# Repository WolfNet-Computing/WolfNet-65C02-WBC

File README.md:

[Pictures](./pictures.html)  
[Connector Pinouts](./pinouts.html)  
[Memory Map](./memory_map.html)  
[Thanks](./thanks.html)

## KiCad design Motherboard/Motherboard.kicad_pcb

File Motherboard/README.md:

# WN-6502-WBC Motherboard

## Pinouts

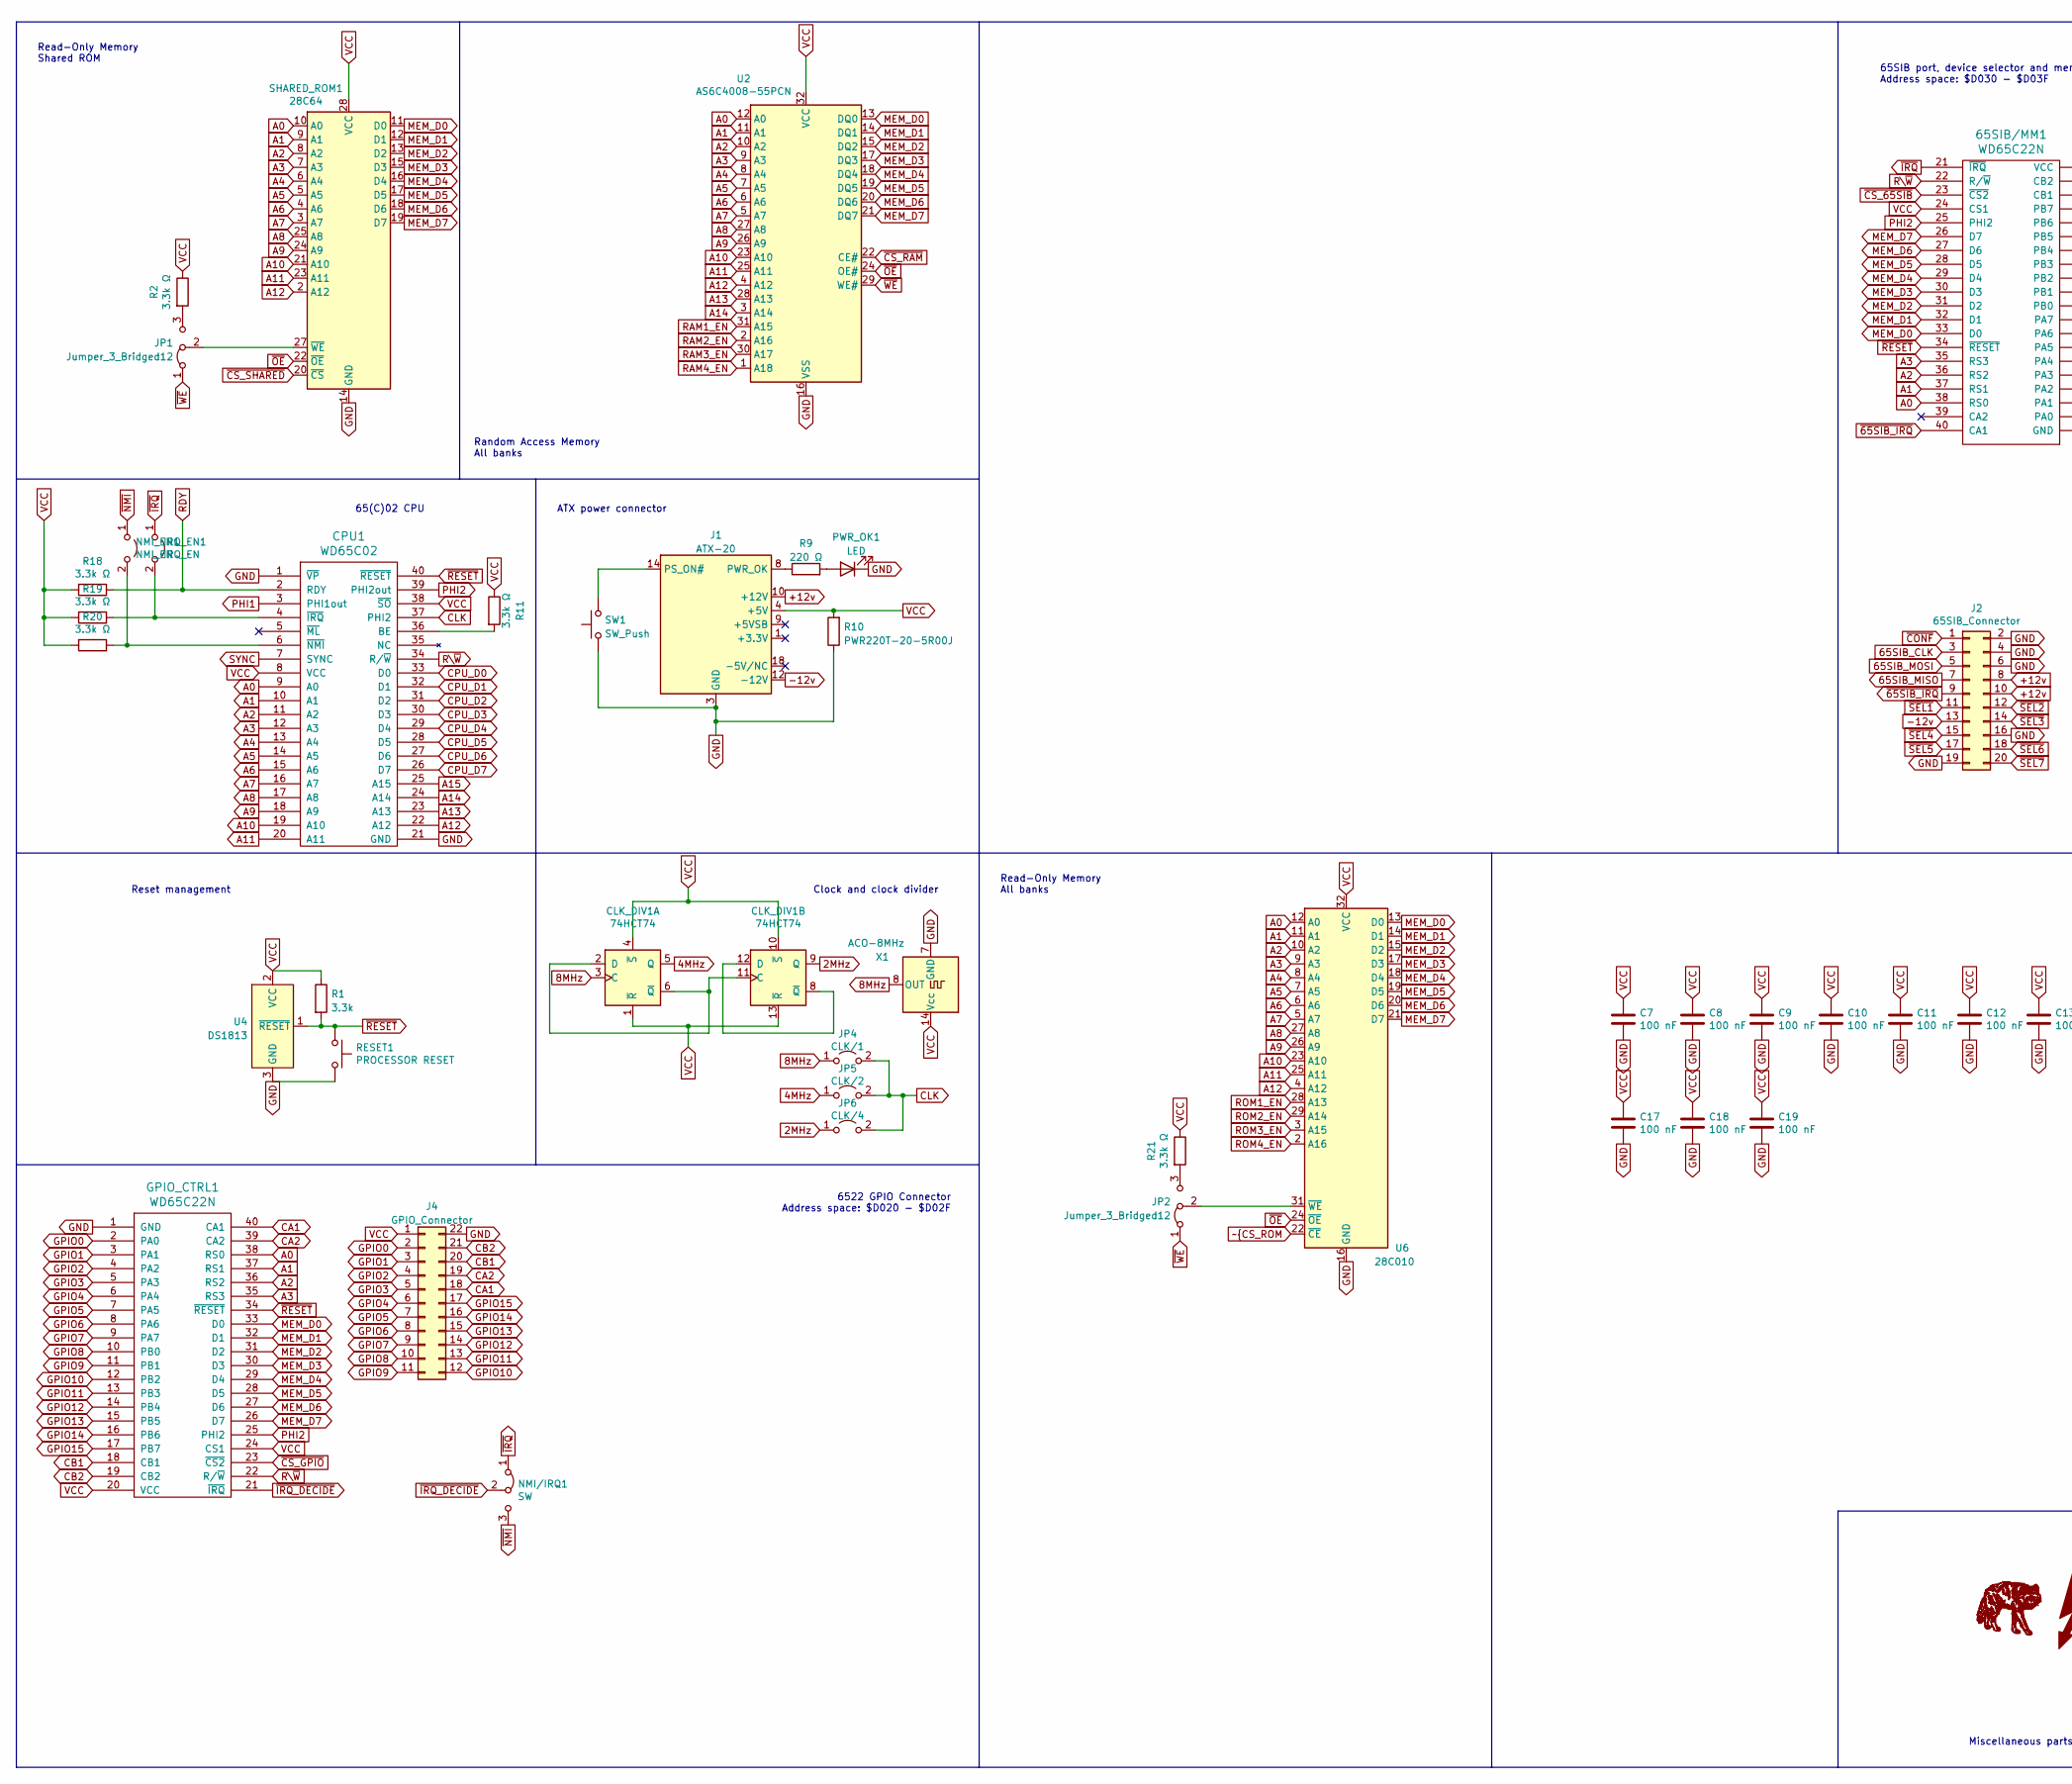
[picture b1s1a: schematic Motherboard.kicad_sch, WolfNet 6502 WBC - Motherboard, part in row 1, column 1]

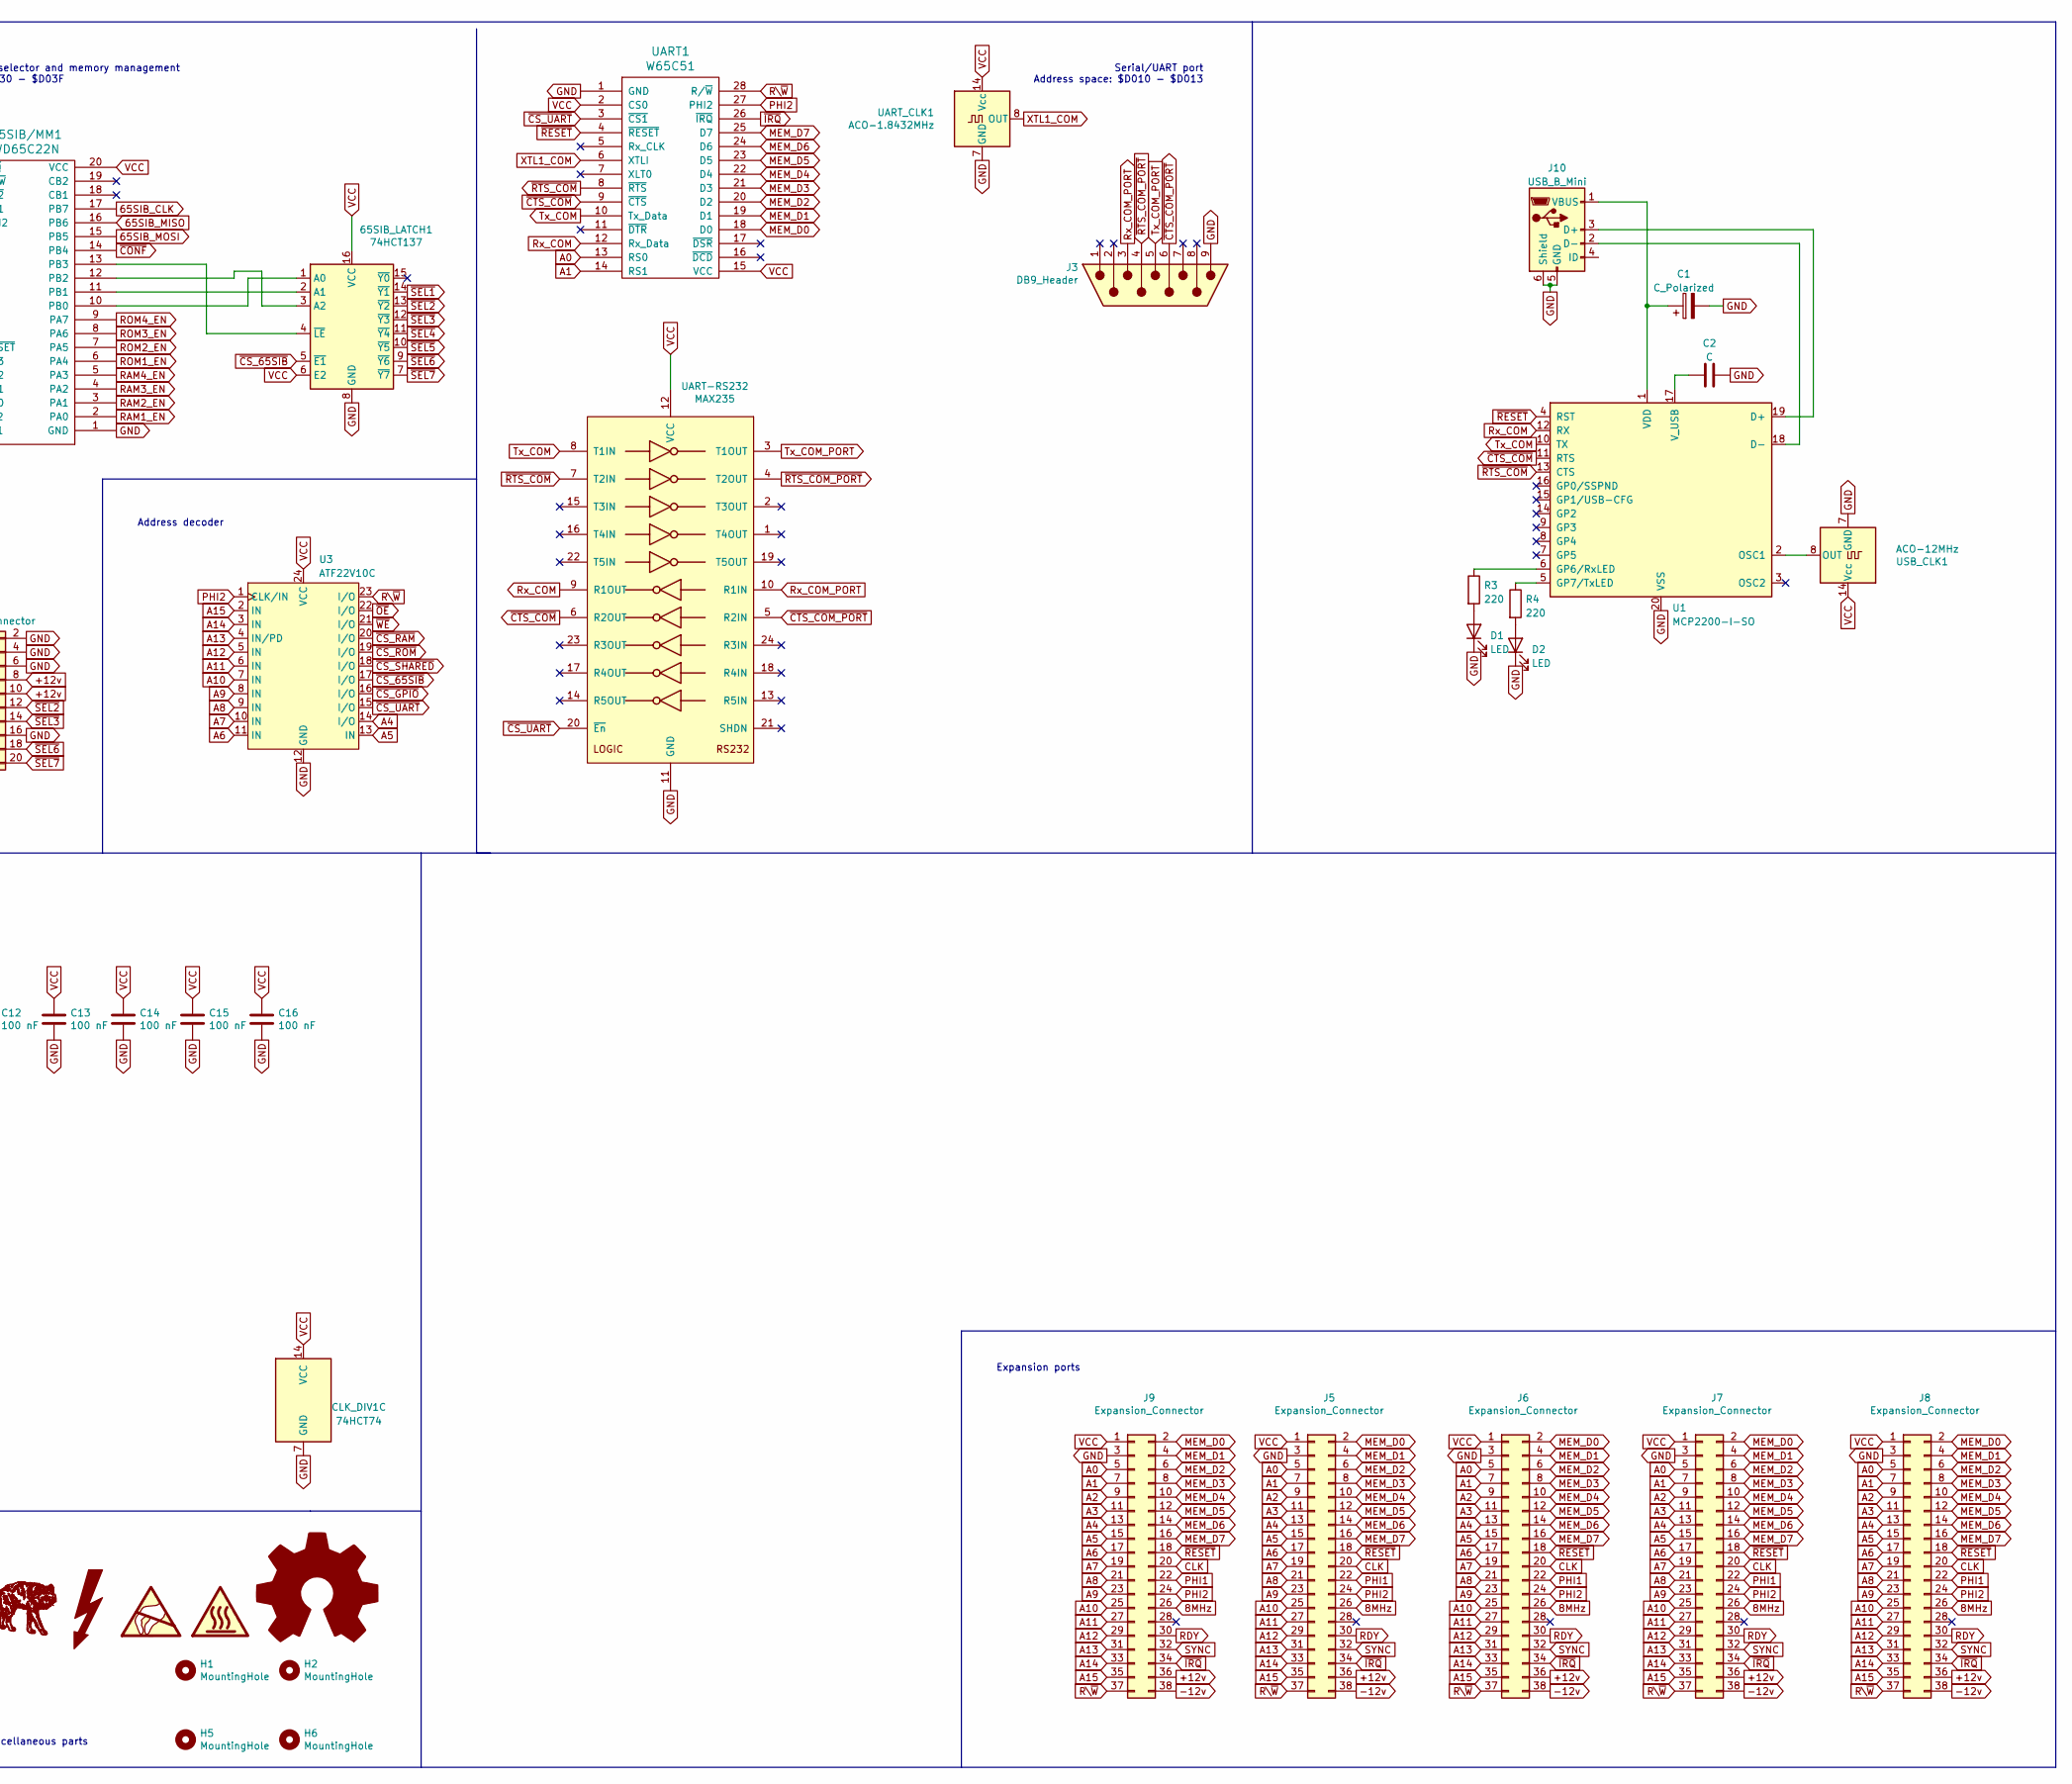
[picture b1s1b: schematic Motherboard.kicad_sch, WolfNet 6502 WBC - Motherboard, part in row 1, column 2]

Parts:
65SIB/MM1: WD65C22N; DIP-40_W15.24mm_Socket_LongPads
65SIB_LATCH1: 74HCT137; DIP-16_W7.62mm_Socket_LongPads
C1: C_Polarized; CP_Radial_D5.0mm_P2.50mm
C2: C; C_Disc_D3.0mm_W1.6mm_P2.50mm
C7, C8, C9, C10, C11, C12, C13, C14, C15, C16, C17, C18, C19: 100 nF; C_Disc_D3.0mm_W1.6mm_P2.50mm
CLK_DIV1: 74HCT74; DIP-14_W7.62mm_Socket_LongPads
CPU1: WD65C02; DIP-40_W15.24mm_Socket_LongPads
D1, D2: LED; LED_D5.0mm
GPIO_CTRL1: WD65C22N; DIP-40_W15.24mm_Socket_LongPads
H1, H2, H5, H6: MountingHole; MountingHole_3.2mm_M3
IRQ_EN1: IRQ_EN; PinHeader_1x02_P2.54mm_Vertical
J1: ATX-20; Molex_Mini-Fit_Jr_5566-20A_2x10_P4.20mm_Vertical
J2: 65SIB_Connector; IDC-Header_2x10-1MP_P2.54mm_Latch6.5mm_Vertical
J3: DB9_Header
J4: GPIO_Connector; PinHeader_2x11_P2.54mm_Vertical
J5, J6, J7, J8, J9: Expansion_Connector; Expansion_Connector_Motherboard
J10: USB_B_Mini; USB_Mini-B_Tensility_54-00023_Vertical
JP1, JP2: Jumper_3_Bridged12; PinHeader_1x03_P2.54mm_Vertical
JP4: CLK/1; PinHeader_1x02_P2.54mm_Vertical
JP5: CLK/2; PinHeader_1x02_P2.54mm_Vertical
JP6: CLK/4; PinHeader_1x02_P2.54mm_Vertical
NMI/IRQ1: SW; PinHeader_1x03_P2.54mm_Vertical
NMI_EN1: NMI_EN; PinHeader_1x02_P2.54mm_Vertical
PWR_OK1: LED; LED_D5.0mm
R1: 3.3k; R_Axial_DIN0207_L6.3mm_D2.5mm_P7.62mm_Horizontal
R2, R11, R18, R19, R20, R21: 3.3k Ω; R_Axial_DIN0207_L6.3mm_D2.5mm_P7.62mm_Horizontal
R3, R4: 220; R_Axial_DIN0207_L6.3mm_D2.5mm_P7.62mm_Horizontal
R9: 220 Ω; R_Axial_DIN0207_L6.3mm_D2.5mm_P7.62mm_Horizontal
R10: PWR220T-20-5R00J; TO-220-2_Horizontal_TabDown
RESET1: PROCESSOR RESET; SW_PUSH_6mm_H4.3mm
SHARED_ROM1: 28C64; DIP_Socket-28_W11.9_W12.7_W15.24_W17.78_W18.5_3M_228-1277-0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
SW1: SW_Push; SW_PUSH_6mm
U1: MCP2200-I-SO; SOIC-20W_7.5x12.8mm_P1.27mm
U2: AS6C4008-55PCN; DIP-32_W15.24mm
U3: ATF22V10C; DIP-24_W7.62mm_Socket_LongPads
U4: DS1813; TO-92
U6: 28C010; DIP_Socket-32_W11.9_W12.7_W15.24_W17.78_W18.5_3M_232-1285-0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
UART1: W65C51; DIP-28_W15.24mm_Socket_LongPads
UART-RS232: MAX235; DIP-24_W15.24mm_Socket_LongPads
UART_CLK1: ACO-1.8432MHz; Oscillator_DIP-14
USB_CLK1: ACO-12MHz; Oscillator_DIP-14
X1: ACO-8MHz; Oscillator_DIP-14

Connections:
2MHz: CLK_DIV1.9 (Q), JP6.1 (A)
4MHz: CLK_DIV1.5 (Q), JP5.1 (A)
8MHz: CLK_DIV1.3 (C), J5.26, J6.26, J7.26, J8.26, J9.26, JP4.1 (A), X1.8 (OUT)
65SIB_CLK: 65SIB/MM1.17 (PB7), J2.3 (CLK)
65SIB_MISO: 65SIB/MM1.16 (PB6), J2.7 (MISO)
65SIB_MOSI: 65SIB/MM1.15 (PB5), J2.5 (MOSI)
+12v: J1.10 (+12V), J2.8 (12v), J2.10 (12v), J5.36, J6.36, J7.36, J8.36, J9.36
-12v: J1.12 (-12V), J2.13 (-12v), J5.38, J6.38, J7.38, J8.38, J9.38
A0: 65SIB/MM1.38 (RS0), CPU1.9 (A0), GPIO_CTRL1.38 (RS0), J5.5, J6.5, J7.5, J8.5, J9.5, SHARED_ROM1.10 (A0), U2.12 (A0), U6.12 (A0), UART1.13 (RS0)
A1: 65SIB/MM1.37 (RS1), CPU1.10 (A1), GPIO_CTRL1.37 (RS1), J5.7, J6.7, J7.7, J8.7, J9.7, SHARED_ROM1.9 (A1), U2.11 (A1), U6.11 (A1), UART1.14 (RS1)
A2: 65SIB/MM1.36 (RS2), CPU1.11 (A2), GPIO_CTRL1.36 (RS2), J5.9, J6.9, J7.9, J8.9, J9.9, SHARED_ROM1.8 (A2), U2.10 (A2), U6.10 (A2)
A3: 65SIB/MM1.35 (RS3), CPU1.12 (A3), GPIO_CTRL1.35 (RS3), J5.11, J6.11, J7.11, J8.11, J9.11, SHARED_ROM1.7 (A3), U2.9 (A3), U6.9 (A3)
A4: CPU1.13 (A4), J5.13, J6.13, J7.13, J8.13, J9.13, SHARED_ROM1.6 (A4), U2.8 (A4), U3.14 (I/O), U6.8 (A4)
A5: CPU1.14 (A5), J5.15, J6.15, J7.15, J8.15, J9.15, SHARED_ROM1.5 (A5), U2.7 (A5), U3.13 (IN), U6.7 (A5)
A6: CPU1.15 (A6), J5.17, J6.17, J7.17, J8.17, J9.17, SHARED_ROM1.4 (A6), U2.6 (A6), U3.11 (IN), U6.6 (A6)
A7: CPU1.16 (A7), J5.19, J6.19, J7.19, J8.19, J9.19, SHARED_ROM1.3 (A7), U2.5 (A7), U3.10 (IN), U6.5 (A7)
A8: CPU1.17 (A8), J5.21, J6.21, J7.21, J8.21, J9.21, SHARED_ROM1.25 (A8), U2.27 (A8), U3.9 (IN), U6.27 (A8)
A9: CPU1.18 (A9), J5.23, J6.23, J7.23, J8.23, J9.23, SHARED_ROM1.24 (A9), U2.26 (A9), U3.8 (IN), U6.26 (A9)
A10: CPU1.19 (A10), J5.25, J6.25, J7.25, J8.25, J9.25, SHARED_ROM1.21 (A10), U2.23 (A10), U3.7 (IN), U6.23 (A10)
A11: CPU1.20 (A11), J5.27, J6.27, J7.27, J8.27, J9.27, SHARED_ROM1.23 (A11), U2.25 (A11), U3.6 (IN), U6.25 (A11)
A12: CPU1.22 (A12), J5.29, J6.29, J7.29, J8.29, J9.29, SHARED_ROM1.2 (A12), U2.4 (A12), U3.5 (IN), U6.4 (A12)
A13: CPU1.23 (A13), J5.31, J6.31, J7.31, J8.31, J9.31, U2.28 (A13), U3.4 (IN/PD)
A14: CPU1.24 (A14), J5.33, J6.33, J7.33, J8.33, J9.33, U2.3 (A14), U3.3 (IN)
A15: CPU1.25 (A15), J5.35, J6.35, J7.35, J8.35, J9.35, U3.2 (IN)
CA1: GPIO_CTRL1.40 (CA1), J4.18
CA2: GPIO_CTRL1.39 (CA2), J4.19
CB1: GPIO_CTRL1.18 (CB1), J4.20
CB2: GPIO_CTRL1.19 (CB2), J4.21
CLK: CPU1.37 (PHI2), J5.20, J6.20, J7.20, J8.20, J9.20, JP4.2 (B), JP5.2 (B), JP6.2 (B)
CPU_D0: CPU1.33 (D0)
CPU_D1: CPU1.32 (D1)
CPU_D2: CPU1.31 (D2)
CPU_D3: CPU1.30 (D3)
CPU_D4: CPU1.29 (D4)
CPU_D5: CPU1.28 (D5)
CPU_D6: CPU1.27 (D6)
CPU_D7: CPU1.26 (D7)
GND: 65SIB/MM1.1 (GND), 65SIB_LATCH1.8 (GND), C1.2, C2.2, C7.2, C8.2, C9.2, C10.2, C11.2, C12.2, C13.2, C14.2, C15.2, C16.2, C17.2, C18.2, C19.2, CLK_DIV1.7 (GND), CPU1.1 (~VP), CPU1.21 (GND), D1.1 (K), D2.1 (K), GPIO_CTRL1.1 (GND), J1.3 (GND), J1.5 (GND), J1.7 (GND), J1.13 (GND), J1.15 (GND), J1.16 (GND), J1.17 (GND), J2.2 (GND), J2.4 (GND), J2.6 (eGND), J2.16 (GND), J2.19 (GND), J3.9 (5), J4.22, J5.3, J6.3, J7.3, J8.3, J9.3, J10.5 (GND), J10.6 (Shield), PWR_OK1.1 (K), R10.1, RESET1.2, SHARED_ROM1.14 (GND), SW1.1, U1.20 (VSS), U2.16 (VSS), U3.12 (GND), U4.3 (GND), U6.16 (GND), UART1.1 (GND), UART-RS232.11 (GND), UART_CLK1.7 (GND), USB_CLK1.7 (GND), X1.7 (GND)
GPIO0: GPIO_CTRL1.2 (PA0), J4.2
GPIO1: GPIO_CTRL1.3 (PA1), J4.3
GPIO2: GPIO_CTRL1.4 (PA2), J4.4
GPIO3: GPIO_CTRL1.5 (PA3), J4.5
GPIO4: GPIO_CTRL1.6 (PA4), J4.6
GPIO5: GPIO_CTRL1.7 (PA5), J4.7
GPIO6: GPIO_CTRL1.8 (PA6), J4.8
GPIO7: GPIO_CTRL1.9 (PA7), J4.9
GPIO8: GPIO_CTRL1.10 (PB0), J4.10
GPIO9: GPIO_CTRL1.11 (PB1), J4.11
GPIO10: GPIO_CTRL1.12 (PB2), J4.12
GPIO11: GPIO_CTRL1.13 (PB3), J4.13
GPIO12: GPIO_CTRL1.14 (PB4), J4.14
GPIO13: GPIO_CTRL1.15 (PB5), J4.15
GPIO14: GPIO_CTRL1.16 (PB6), J4.16
GPIO15: GPIO_CTRL1.17 (PB7), J4.17
MEM_D0: 65SIB/MM1.33 (D0), GPIO_CTRL1.33 (D0), J5.2, J6.2, J7.2, J8.2, J9.2, SHARED_ROM1.11 (D0), U2.13 (DQ0), U6.13 (D0), UART1.18 (D0)
MEM_D1: 65SIB/MM1.32 (D1), GPIO_CTRL1.32 (D1), J5.4, J6.4, J7.4, J8.4, J9.4, SHARED_ROM1.12 (D1), U2.14 (DQ1), U6.14 (D1), UART1.19 (D1)
MEM_D2: 65SIB/MM1.31 (D2), GPIO_CTRL1.31 (D2), J5.6, J6.6, J7.6, J8.6, J9.6, SHARED_ROM1.13 (D2), U2.15 (DQ2), U6.15 (D2), UART1.20 (D2)
MEM_D3: 65SIB/MM1.30 (D3), GPIO_CTRL1.30 (D3), J5.8, J6.8, J7.8, J8.8, J9.8, SHARED_ROM1.15 (D3), U2.17 (DQ3), U6.17 (D3), UART1.21 (D3)
MEM_D4: 65SIB/MM1.29 (D4), GPIO_CTRL1.29 (D4), J5.10, J6.10, J7.10, J8.10, J9.10, SHARED_ROM1.16 (D4), U2.18 (DQ4), U6.18 (D4), UART1.22 (D4)
MEM_D5: 65SIB/MM1.28 (D5), GPIO_CTRL1.28 (D5), J5.12, J6.12, J7.12, J8.12, J9.12, SHARED_ROM1.17 (D5), U2.19 (DQ5), U6.19 (D5), UART1.23 (D5)
MEM_D6: 65SIB/MM1.27 (D6), GPIO_CTRL1.27 (D6), J5.14, J6.14, J7.14, J8.14, J9.14, SHARED_ROM1.18 (D6), U2.20 (DQ6), U6.20 (D6), UART1.24 (D6)
MEM_D7: 65SIB/MM1.26 (D7), GPIO_CTRL1.26 (D7), J5.16, J6.16, J7.16, J8.16, J9.16, SHARED_ROM1.19 (D7), U2.21 (DQ7), U6.21 (D7), UART1.25 (D7)
unnamed: 65SIB/MM1.10 (PB0), 65SIB_LATCH1.1 (A0)
unnamed: 65SIB/MM1.11 (PB1), 65SIB_LATCH1.2 (A1)
unnamed: 65SIB/MM1.12 (PB2), 65SIB_LATCH1.3 (A2)
unnamed: 65SIB/MM1.13 (PB3), 65SIB_LATCH1.4 (~LE)
unnamed: CLK_DIV1.2 (D), CLK_DIV1.6 (~Q), CLK_DIV1.11 (C)
unnamed: CLK_DIV1.8 (~Q), CLK_DIV1.12 (D)
unnamed: CPU1.36 (BE), R11.2
unnamed: CPU1.4 (~IRQ), IRQ_EN1.2 (B), R19.1
unnamed: CPU1.6 (~NMI), NMI_EN1.2 (B), R20.1
unnamed: D1.2 (A), R3.2
unnamed: D2.2 (A), R4.2
unnamed: J1.14 (PS_ON#), SW1.2
unnamed: J1.8 (PWR_OK), R9.1
unnamed: J10.3 (D+), U1.19 (D+)
unnamed: J10.2 (D-), U1.18 (D-)
unnamed: C1.1, J10.1 (VBUS), U1.1 (VDD)
unnamed: JP1.3 (B), R2.2
unnamed: JP1.2 (C), SHARED_ROM1.27 (~WE)
unnamed: JP2.3 (B), R21.2
unnamed: JP2.2 (C), U6.31 (~WE)
unnamed: PWR_OK1.2 (A), R9.2
unnamed: R3.1, U1.6 (GP6/RxLED)
unnamed: R4.1, U1.5 (GP7/TxLED)
unnamed: U1.2 (OSC1), USB_CLK1.8 (OUT)
unnamed: C2.1, U1.17 (V_USB)
PHI1: CPU1.3 (PHI1out), J5.22, J6.22, J7.22, J8.22, J9.22
PHI2: 65SIB/MM1.25 (PHI2), CPU1.39 (PHI2out), GPIO_CTRL1.25 (PHI2), J5.24, J6.24, J7.24, J8.24, J9.24, U3.1 (CLK/IN), UART1.27 (PHI2)
RAM1_EN: 65SIB/MM1.2 (PA0), U2.31 (A15)
RAM2_EN: 65SIB/MM1.3 (PA1), U2.2 (A16)
RAM3_EN: 65SIB/MM1.4 (PA2), U2.30 (A17)
RAM4_EN: 65SIB/MM1.5 (PA3), U2.1 (A18)
RDY: CPU1.2 (RDY), J5.30, J6.30, J7.30, J8.30, J9.30, R18.1
ROM1_EN: 65SIB/MM1.6 (PA4), U6.28 (A13)
ROM2_EN: 65SIB/MM1.7 (PA5), U6.29 (A14)
ROM3_EN: 65SIB/MM1.8 (PA6), U6.3 (A15)
ROM4_EN: 65SIB/MM1.9 (PA7), U6.2 (A16)
R\~W: 65SIB/MM1.22 (R/~W), CPU1.34 (R/~W), GPIO_CTRL1.22 (R/~W), J5.37, J6.37, J7.37, J8.37, J9.37, U3.23 (I/O), UART1.28 (R/~W)
Rx_COM: U1.12 (RX), UART1.12 (Rx_Data), UART-RS232.9 (R1OUT)
Rx_COM_PORT: J3.3 (2), UART-RS232.10 (R1IN)
SYNC: CPU1.7 (SYNC), J5.32, J6.32, J7.32, J8.32, J9.32
Tx_COM: U1.10 (TX), UART1.10 (Tx_Data), UART-RS232.8 (T1IN)
Tx_COM_PORT: J3.5 (3), UART-RS232.3 (T1OUT)
VCC: 65SIB/MM1.20 (VCC), 65SIB/MM1.24 (CS1), 65SIB_LATCH1.6 (E2), 65SIB_LATCH1.16 (VCC), C7.1, C8.1, C9.1, C10.1, C11.1, C12.1, C13.1, C14.1, C15.1, C16.1, C17.1, C18.1, C19.1, CLK_DIV1.1 (~R), CLK_DIV1.4 (~S), CLK_DIV1.10 (~S), CLK_DIV1.13 (~R), CLK_DIV1.14 (VCC), CPU1.8 (VCC), CPU1.38 (~SO), GPIO_CTRL1.20 (VCC), GPIO_CTRL1.24 (CS1), J1.4 (+5V), J1.6 (+5V), J1.19 (+5V), J1.20 (+5V), J4.1, J5.1, J6.1, J7.1, J8.1, J9.1, R1.1, R2.1, R10.2, R11.1, R18.2, R19.2, R20.2, R21.1, SHARED_ROM1.28 (VCC), U2.32 (VCC), U3.24 (VCC), U4.2 (VCC), U6.32 (VCC), UART1.2 (CS0), UART1.15 (VCC), UART-RS232.12 (VCC), UART_CLK1.14 (Vcc), USB_CLK1.14 (Vcc), X1.14 (Vcc)
XTL1_COM: UART1.6 (XTLI), UART_CLK1.8 (OUT)
~65SIB_IRQ: 65SIB/MM1.40 (CA1), J2.9 (IRO\)
~CONF: 65SIB/MM1.14 (PB4), J2.1 (CONF\)
~CS_65SIB: 65SIB/MM1.23 (~CS2), 65SIB_LATCH1.5 (~E1), U3.17 (I/O)
~CS_GPIO: GPIO_CTRL1.23 (~CS2), U3.16 (I/O)
~CS_RAM: U2.22 (CE#), U3.20 (I/O)
~{CS_ROM: U6.22 (~CE)
~CS_ROM: U3.19 (I/O)
~CS_SHARED: SHARED_ROM1.20 (~CS), U3.18 (I/O)
~CS_UART: U3.15 (I/O), UART1.3 (~CS1), UART-RS232.20 (~En)
~CTS_COM_PORT: J3.6 (8), UART-RS232.5 (R2IN)
~CTS_COM: U1.11 (RTS), UART1.9 (~CTS), UART-RS232.6 (R2OUT)
~IRQ_DECIDE: GPIO_CTRL1.21 (~IRQ), NMI/IRQ1.2 (C)
~IRQ: 65SIB/MM1.21 (~IRQ), IRQ_EN1.1 (A), J5.34, J6.34, J7.34, J8.34, J9.34, NMI/IRQ1.1 (A), UART1.26 (~IRQ)
~NMI: NMI/IRQ1.3 (B), NMI_EN1.1 (A)
~OE: SHARED_ROM1.22 (~OE), U2.24 (OE#), U3.22 (I/O), U6.24 (~OE)
~RESET: 65SIB/MM1.34 (~RESET), CPU1.40 (~RESET), GPIO_CTRL1.34 (~RESET), J5.18, J6.18, J7.18, J8.18, J9.18, R1.2, RESET1.1, U1.4 (RST), U4.1 (~RESET), UART1.4 (~RESET)
~RTS_COM_PORT: J3.4 (7), UART-RS232.4 (T2OUT)
~RTS_COM: U1.13 (CTS), UART1.8 (~RTS), UART-RS232.7 (T2IN)
~SEL1: 65SIB_LATCH1.14 (~Y1), J2.11 (SEL1\)
~SEL2: 65SIB_LATCH1.13 (~Y2), J2.12 (SEL2\)
~SEL3: 65SIB_LATCH1.12 (~Y3), J2.14 (SEL3\)
~SEL4: 65SIB_LATCH1.11 (~Y4), J2.15 (SEL4\)
~SEL5: 65SIB_LATCH1.10 (~Y5), J2.17 (SEL5\)
~SEL6: 65SIB_LATCH1.9 (~Y6), J2.18 (SEL6\)
~SEL7: 65SIB_LATCH1.7 (~Y7), J2.20 (SEL7\)
~WE: JP1.1 (A), JP2.1 (A), U2.29 (WE#), U3.21 (I/O)

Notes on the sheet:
ATX power connector
Expansion ports
Clock and clock divider
Miscellaneous parts
Serial/UART port Address space: $D010 - $D013
65(C)02 CPU
65SIB port, device selector and memory management Address space: $D030 - $D03F
Read-Only Memory All banks
Read-Only Memory Shared ROM
6522 GPIO Connector Address space: $D020 - $D02F
Random Access Memory All banks
Reset management
Address decoder

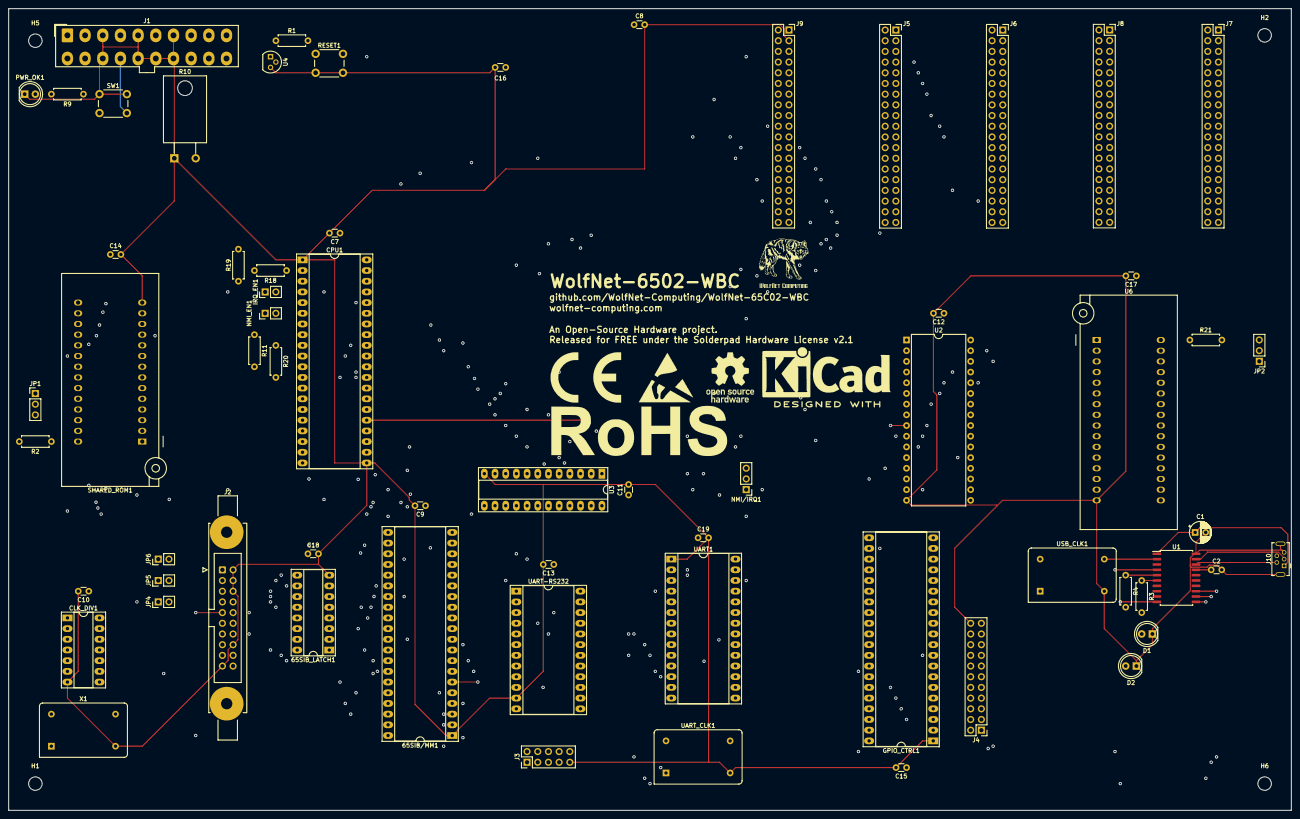
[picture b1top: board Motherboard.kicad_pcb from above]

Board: 8 copper layers, 304.8 x 190.5 mm, 69 parts (0 on the bottom side), 122 nets.

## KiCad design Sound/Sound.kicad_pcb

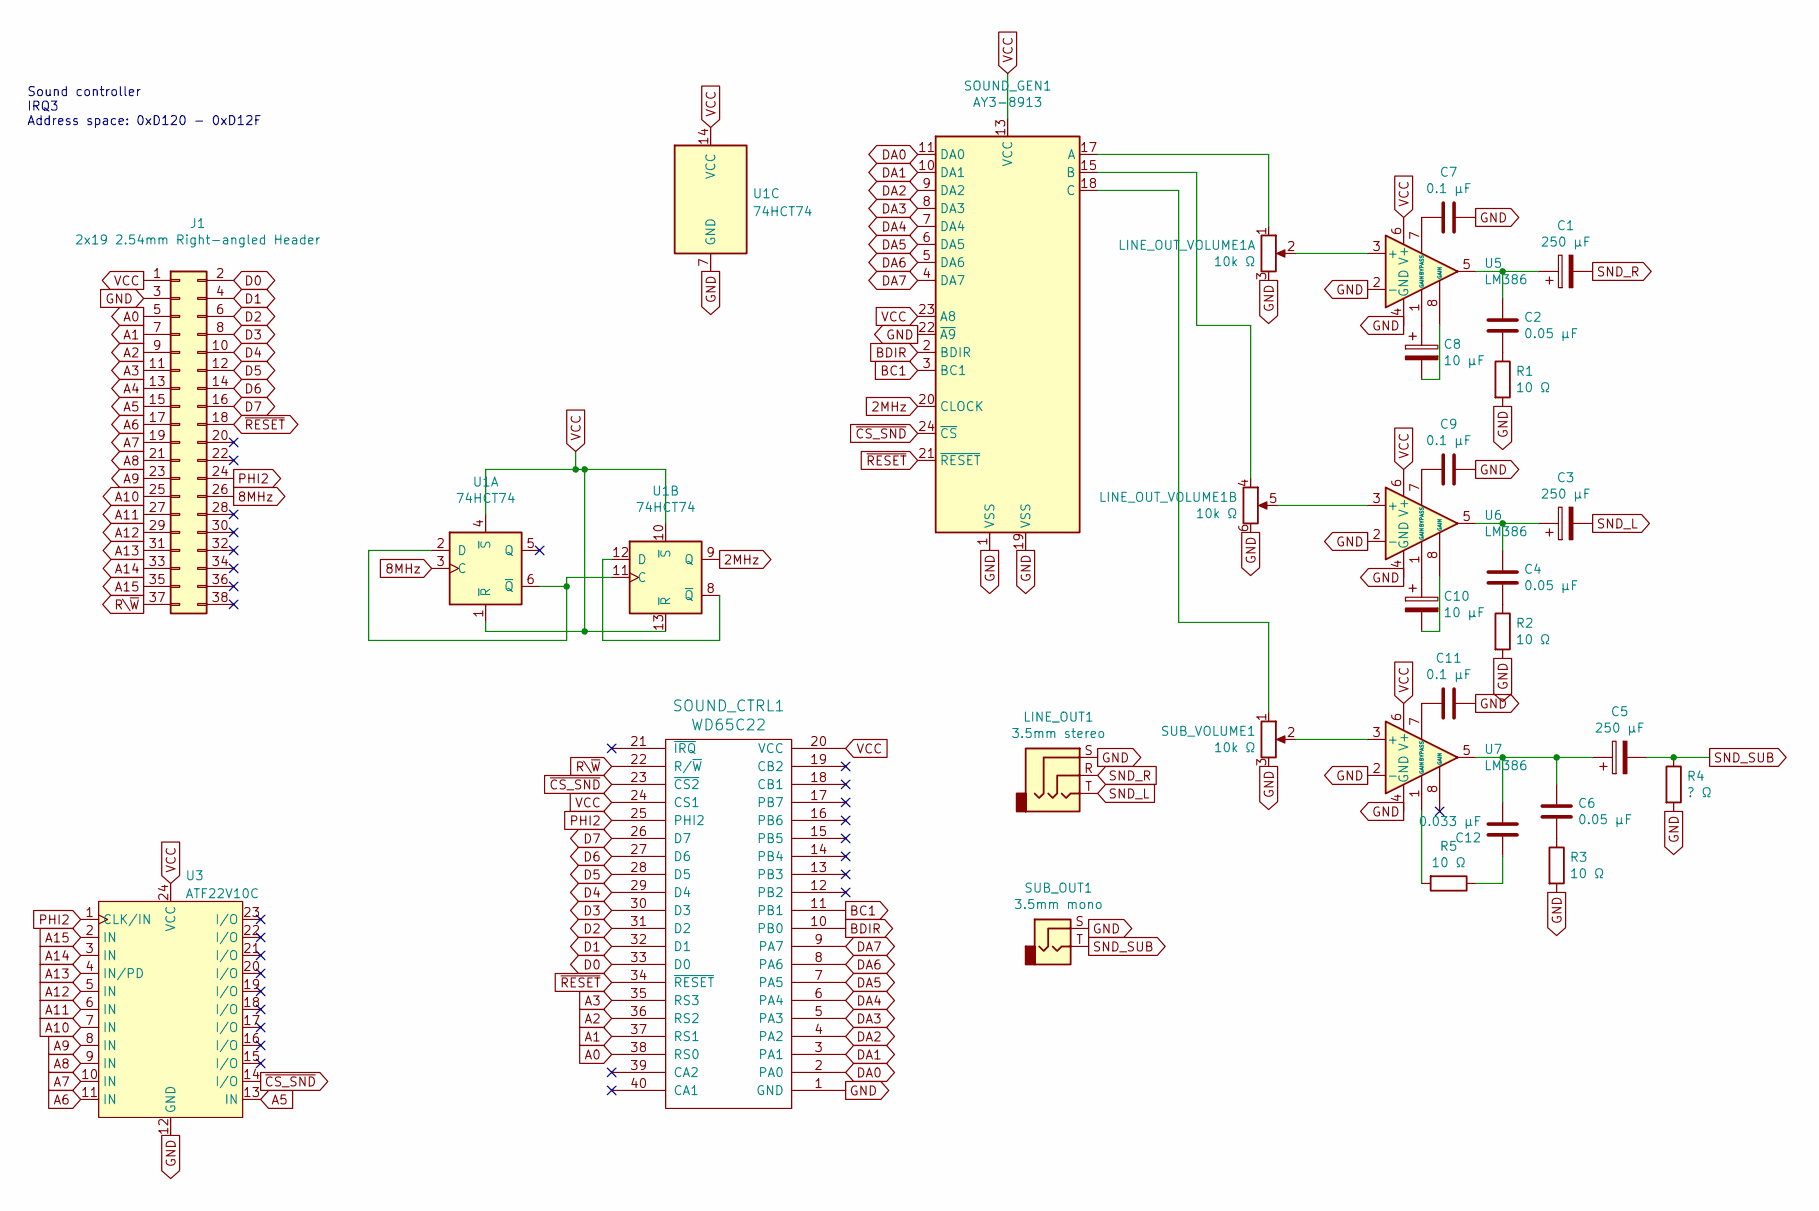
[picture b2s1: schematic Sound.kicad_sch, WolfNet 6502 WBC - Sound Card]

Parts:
C1, C3, C5: 250 µF; CP_Radial_D5.0mm_P2.50mm
C2, C4, C6: 0.05 µF; C_Disc_D3.0mm_W2.0mm_P2.50mm
C7, C9, C11: 0.1 µF; C_Disc_D3.0mm_W2.0mm_P2.50mm
C8, C10: 10 µF; CP_Radial_D5.0mm_P2.50mm
C12: 0.033 µF; C_Disc_D3.0mm_W2.0mm_P2.50mm
J1: 2x19 2.54mm Right-angled Header; Expansion_Connector_Board
LINE_OUT1: 3.5mm stereo; Jack_3.5mm_CUI_SJ1-3533NG_Horizontal
LINE_OUT_VOLUME1: 10k Ω; Potentiometer_Piher_T-16H_Double_Horizontal
R1, R2, R3, R5: 10 Ω; R_Axial_DIN0204_L3.6mm_D1.6mm_P5.08mm_Horizontal
R4: ? Ω; R_Axial_DIN0204_L3.6mm_D1.6mm_P5.08mm_Horizontal
SOUND_CTRL1: WD65C22; DIP-40_W15.24mm_Socket_LongPads
SOUND_GEN1: AY3-8913; DIP-24_W15.24mm_Socket_LongPads
SUB_OUT1: 3.5mm mono; Jack_3.5mm_CUI_SJ1-3533NG_Horizontal
SUB_VOLUME1: 10k Ω; Potentiometer_Piher_T-16H_Single_Horizontal
U1: 74HCT74; DIP-14_W7.62mm_Socket_LongPads
U3: ATF22V10C; DIP-24_W7.62mm_Socket_LongPads
U5, U6, U7: LM386; DIP-8_W7.62mm_Socket_LongPads

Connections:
2MHz: SOUND_GEN1.20 (CLOCK), U1.9 (Q)
8MHz: J1.26, U1.3 (C)
A0: J1.5, SOUND_CTRL1.38 (RS0)
A1: J1.7, SOUND_CTRL1.37 (RS1)
A2: J1.9, SOUND_CTRL1.36 (RS2)
A3: J1.11, SOUND_CTRL1.35 (RS3)
A4: J1.13
A5: J1.15, U3.13 (IN)
A6: J1.17, U3.11 (IN)
A7: J1.19, U3.10 (IN)
A8: J1.21, U3.9 (IN)
A9: J1.23, U3.8 (IN)
A10: J1.25, U3.7 (IN)
A11: J1.27, U3.6 (IN)
A12: J1.29, U3.5 (IN)
A13: J1.31, U3.4 (IN/PD)
A14: J1.33, U3.3 (IN)
A15: J1.35, U3.2 (IN)
BC1: SOUND_CTRL1.11 (PB1), SOUND_GEN1.3 (BC1)
BDIR: SOUND_CTRL1.10 (PB0), SOUND_GEN1.2 (BDIR)
D0: J1.2, SOUND_CTRL1.33 (D0)
D1: J1.4, SOUND_CTRL1.32 (D1)
D2: J1.6, SOUND_CTRL1.31 (D2)
D3: J1.8, SOUND_CTRL1.30 (D3)
D4: J1.10, SOUND_CTRL1.29 (D4)
D5: J1.12, SOUND_CTRL1.28 (D5)
D6: J1.14, SOUND_CTRL1.27 (D6)
D7: J1.16, SOUND_CTRL1.26 (D7)
DA0: SOUND_CTRL1.2 (PA0), SOUND_GEN1.11 (DA0)
DA1: SOUND_CTRL1.3 (PA1), SOUND_GEN1.10 (DA1)
DA2: SOUND_CTRL1.4 (PA2), SOUND_GEN1.9 (DA2)
DA3: SOUND_CTRL1.5 (PA3), SOUND_GEN1.8 (DA3)
DA4: SOUND_CTRL1.6 (PA4), SOUND_GEN1.7 (DA4)
DA5: SOUND_CTRL1.7 (PA5), SOUND_GEN1.6 (DA5)
DA6: SOUND_CTRL1.8 (PA6), SOUND_GEN1.5 (DA6)
DA7: SOUND_CTRL1.9 (PA7), SOUND_GEN1.4 (DA7)
GND: C7.1, C9.1, C11.1, J1.3, LINE_OUT1.S, LINE_OUT_VOLUME1.3, LINE_OUT_VOLUME1.6, R1.2, R2.2, R3.2, R4.2, SOUND_CTRL1.1 (GND), SOUND_GEN1.1 (VSS), SOUND_GEN1.19 (VSS), SOUND_GEN1.22 (~A9), SUB_OUT1.S, SUB_VOLUME1.3, U1.7 (GND), U3.12 (GND), U5.2 (-), U5.4 (GND), U6.2 (-), U6.4 (GND), U7.2 (-), U7.4 (GND)
unnamed: C1.1, C2.1, U5.5
unnamed: C2.2, R1.1
unnamed: C3.1, C4.1, U6.5
unnamed: C4.2, R2.1
unnamed: C6.2, R3.1
unnamed: C8.1, U5.1 (GAIN)
unnamed: C8.2, U5.8 (GAIN)
unnamed: C10.1, U6.1 (GAIN)
unnamed: C10.2, U6.8 (GAIN)
unnamed: C12.1, R5.1
unnamed: C5.1, C6.1, C12.2, U7.5
unnamed: R5.2, U7.1 (GAIN)
unnamed: LINE_OUT_VOLUME1.1, SOUND_GEN1.17 (A)
unnamed: LINE_OUT_VOLUME1.4, SOUND_GEN1.15 (B)
unnamed: SOUND_GEN1.18 (C), SUB_VOLUME1.1
unnamed: U1.2 (D), U1.6 (~Q), U1.11 (C)
unnamed: U1.8 (~Q), U1.12 (D)
unnamed: LINE_OUT_VOLUME1.2, U5.3 (+)
unnamed: C7.2, U5.7 (BYPASS)
unnamed: LINE_OUT_VOLUME1.5, U6.3 (+)
unnamed: C9.2, U6.7 (BYPASS)
unnamed: SUB_VOLUME1.2, U7.3 (+)
unnamed: C11.2, U7.7 (BYPASS)
PHI2: J1.24, SOUND_CTRL1.25 (PHI2), U3.1 (CLK/IN)
R\~W: J1.37, SOUND_CTRL1.22 (R/~W)
SND_L: C3.2, LINE_OUT1.T
SND_R: C1.2, LINE_OUT1.R
SND_SUB: C5.2, R4.1, SUB_OUT1.T
VCC: J1.1, SOUND_CTRL1.20 (VCC), SOUND_CTRL1.24 (CS1), SOUND_GEN1.13 (VCC), SOUND_GEN1.23 (A8), U1.1 (~R), U1.4 (~S), U1.10 (~S), U1.13 (~R), U1.14 (VCC), U3.24 (VCC), U5.6 (V+), U6.6 (V+), U7.6 (V+)
~CS_SND: SOUND_CTRL1.23 (~CS2), SOUND_GEN1.24 (~CS), U3.14 (I/O)
~RESET: J1.18, SOUND_CTRL1.34 (~RESET), SOUND_GEN1.21 (~RESET)

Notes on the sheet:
Sound controller IRQ3 Address space: 0xD120 - 0xD12F

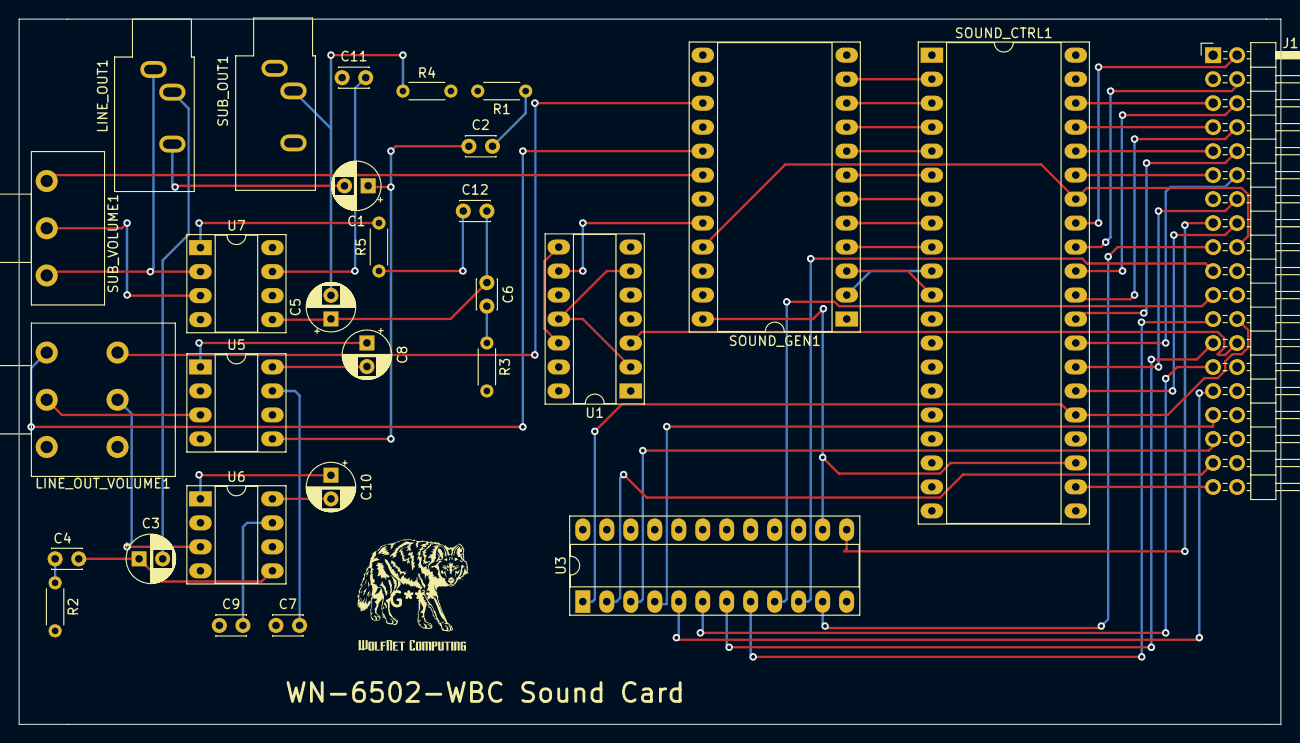
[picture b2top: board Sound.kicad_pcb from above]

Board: 4 copper layers, 133.6 x 74.7 mm, 29 parts (0 on the bottom side), 67 nets.

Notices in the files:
Motherboard/Motherboard.kicad_pcb:
Released for FREE under the Solderpad Hardware License v2.1
